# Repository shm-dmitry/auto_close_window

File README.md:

This project allows auto-open and auto-close your windows.
Project consists schematics of 3 modules and firmware for 2 controllers

Project re-started

In-door modules:
==============

1. Placed on window neare handle. It controls handle state (via hall sensor and magnet) and allows to you to push button open or close manually
Also this module connected to WIFI and allows to to control your window from any smart house server (via MQTT protocol).
2. Placed on up-side window frame. Contains servo, receives commands from module#1 and executes it.

Out-door module:
==============

1. Listen for a noise and check air quality. 

Project status
==============

| Hardware | status |
| ---- | ---- |
| Indoor schema :: near-handle module | no |
| Indoor schema :: servo module | no |
| Indoor schema :: digital channel to outdoor schema | no |
| Outdoor module schema :: microcontroller and its periphery | no |
| Outdoor module schema :: sensors | no |

| Board | status |
| ---- | ---- |
| Indoor board :: near-handle module | no |
| Indoor board :: servo module | no |
| Outdoor module board | no |

| Firmware | status |
| ---- | ---- |
| Indoor firmware :: hardware sensors - hall, switch and soft lock | no |
| Indoor firmware :: buttons | no |
| Indoor firmware :: servo control and calibration | no |
| Indoor firmware :: led indication | no |
| Indoor firmware :: controller | no |
| Outdoor firmware :: BMP280 | no |
| Outdoor firmware :: SGP30 | no |
| Outdoor firmware :: Noise sensor | no |
| Outdoor firmware :: Sensor value filters and controller | no |
| Outdoor firmware :: Data transmitter | no |

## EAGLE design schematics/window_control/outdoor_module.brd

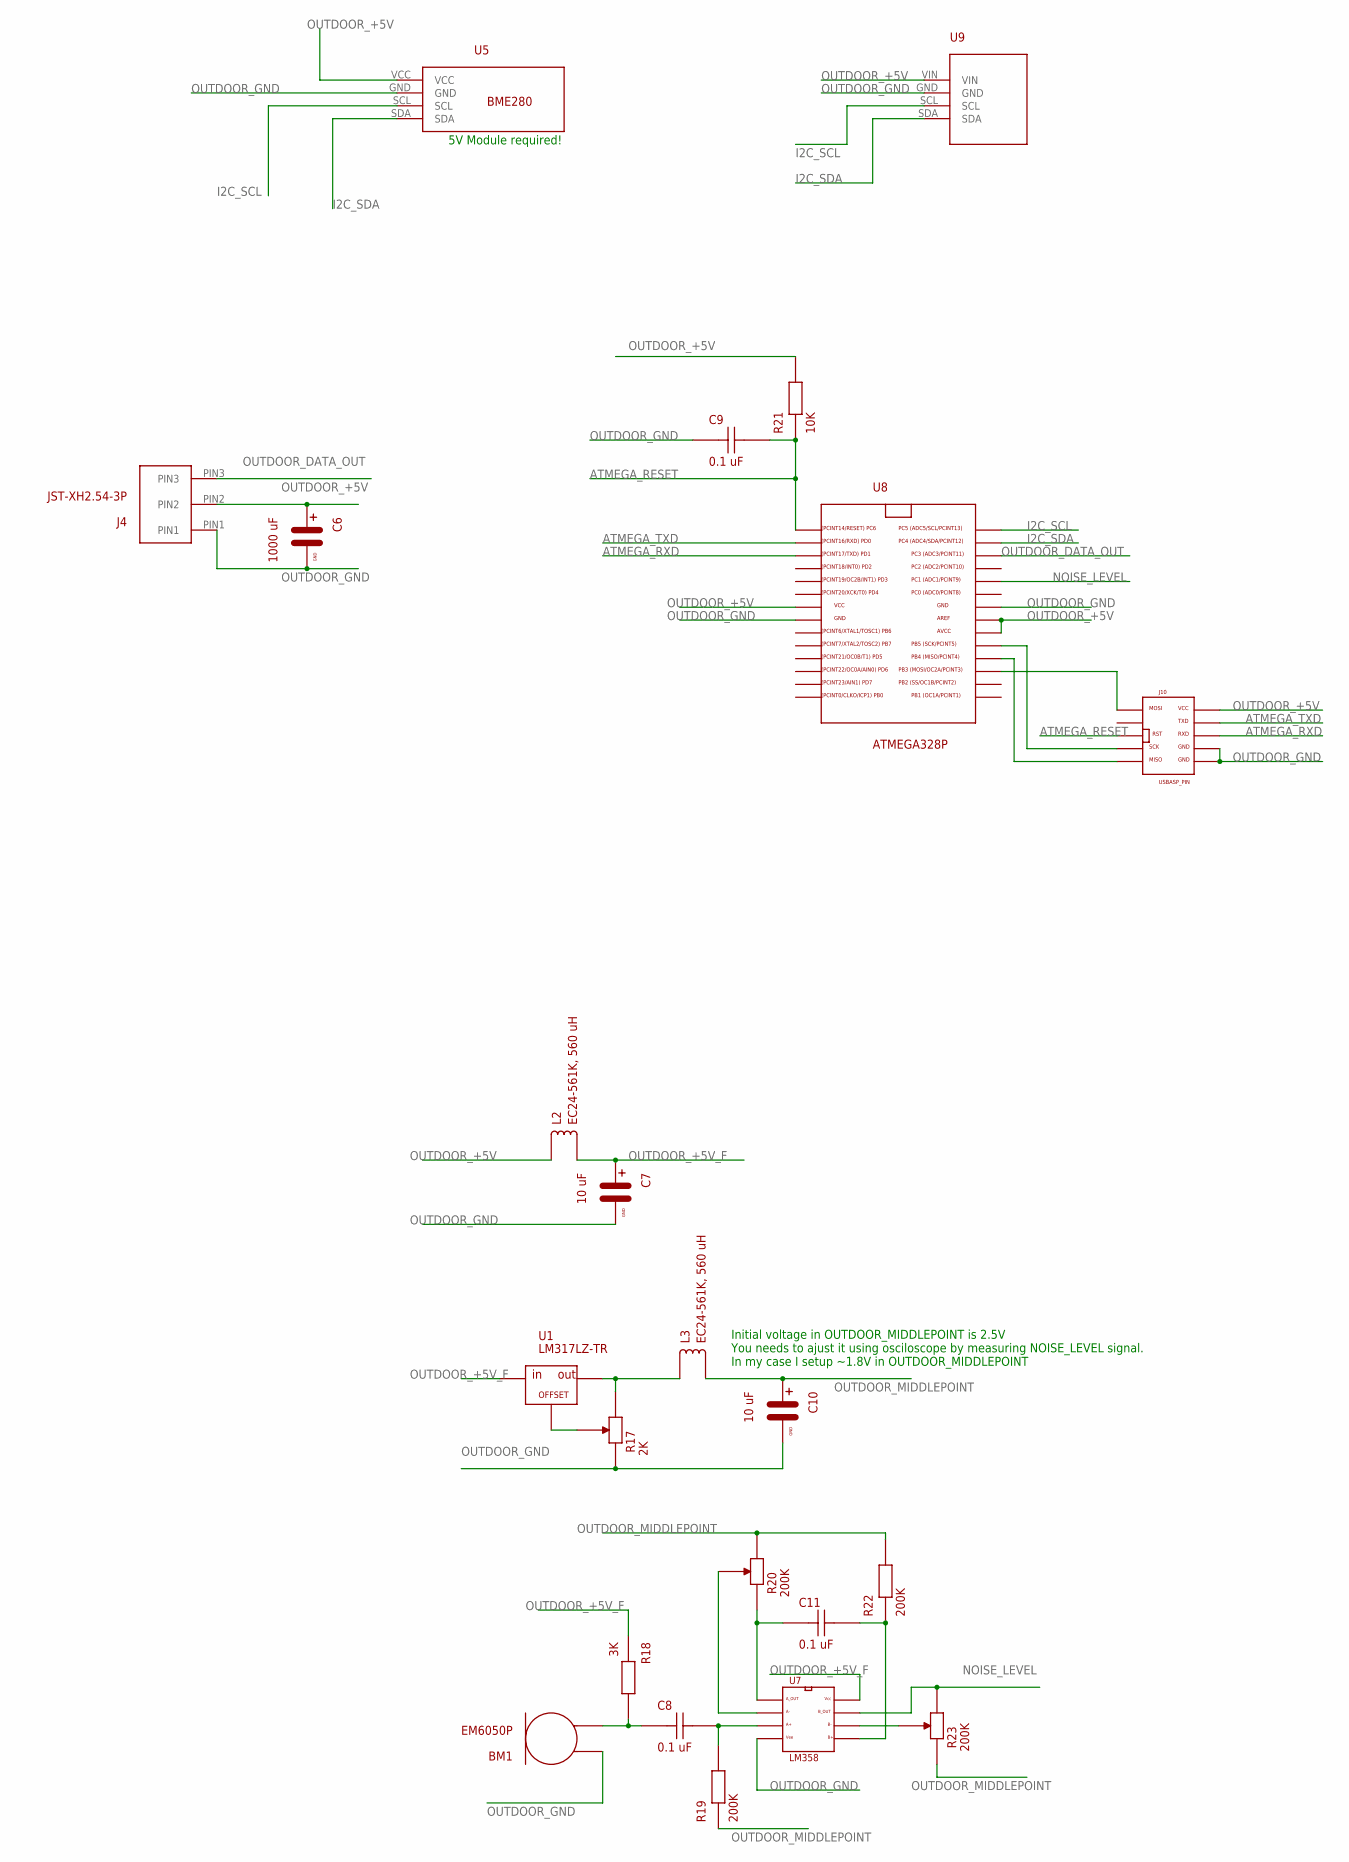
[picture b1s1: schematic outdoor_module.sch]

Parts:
BM1: EM6050P; MICROPHONE
C6: 1000 uF; C
C7, C10: 10 uF; C
C8, C9, C11: 0.1 uF; C-1
J4: JST-XH2.54-3P; JST-XH254-3P
J10: USBASP_PIN
L2, L3: EC24-561K, 560 uH; L-EC24
R17: 2K; RD-3362H
R18: 3K; R
R19, R22: 200K; R
R20, R23: 200K; RD-3296Z
R21: 10K; R
U1: LM317LZ-TR; TO-92
U5: BMP280 5V module; BME280-CONNECTOR-ONLY
U7: LM358; DIP8
U8: ATMEGA328P
U9: GY-SGP30

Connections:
ATMEGA_RESET: C9.P$2, J10.RST (RESET), R21.P$1, U8.PC6
ATMEGA_RXD: J10.RXD, U8.PD1
ATMEGA_TXD: J10.TXD, U8.PD0
I2C_SCL: U5.SCL, U8.PC5, U9.SCL
I2C_SDA: U5.SDA, U8.PC4, U9.SDA
unnamed: BM1.P$2, C8.P$1, R18.P$2
unnamed: C8.P$2, R19.P$2, U7.PIN_3 (A+)
unnamed: R17.P3, U1.P3 (GND)
unnamed: C11.P$1, R20.P1, U7.PIN_1 (A_OUT)
unnamed: R23.P3, U7.PIN_6 (B-)
unnamed: C11.P$2, R22.P$1, U7.PIN_5 (B+)
unnamed: R20.P3, U7.PIN_2 (A-)
unnamed: J10.MOSI, U8.PB3
unnamed: J10.MISO, U8.PB4
unnamed: J10.SCK, U8.PB5
NOISE_LEVEL: R23.P2, U7.PIN_7 (B_OUT), U8.PC1
OUT: L3.P$1, R17.P2, U1.P2 (OUT)
OUTDOOR_+5V: C6.PIN_PLUS, J4.PIN2, J10.VCC, L2.P$1, R21.P$2, U5.VCC, U8.AREF, U8.AVCC, U8.VCC, U9.VIN
OUTDOOR_+5V_F: C7.PIN_PLUS, L2.P$2, R18.P$1, U1.P1 (IN), U7.PIN_8 (VCC)
OUTDOOR_DATA_OUT: J4.PIN3, U8.PC3
OUTDOOR_GND: BM1.P$1, C6.PIN_GND, C7.PIN_GND, C9.P$1, C10.PIN_GND, J4.PIN1, J10.GND, J10.GND1, R17.P1, U5.GND, U7.PIN_4 (VEE), U8.GND, U8.GND1, U9.GND
OUTDOOR_MIDDLEPOINT: C10.PIN_PLUS, L3.P$2, R19.P$1, R20.P2, R22.P$2, R23.P1

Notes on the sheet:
5V Module required!
Initial voltage in OUTDOOR_MIDDLEPOINT is 2.5V You needs to ajust it using osciloscope by measuring NOISE_LEVEL signal. In my case I setup ~1.8V in OUTDOOR_MIDDLEPOINT

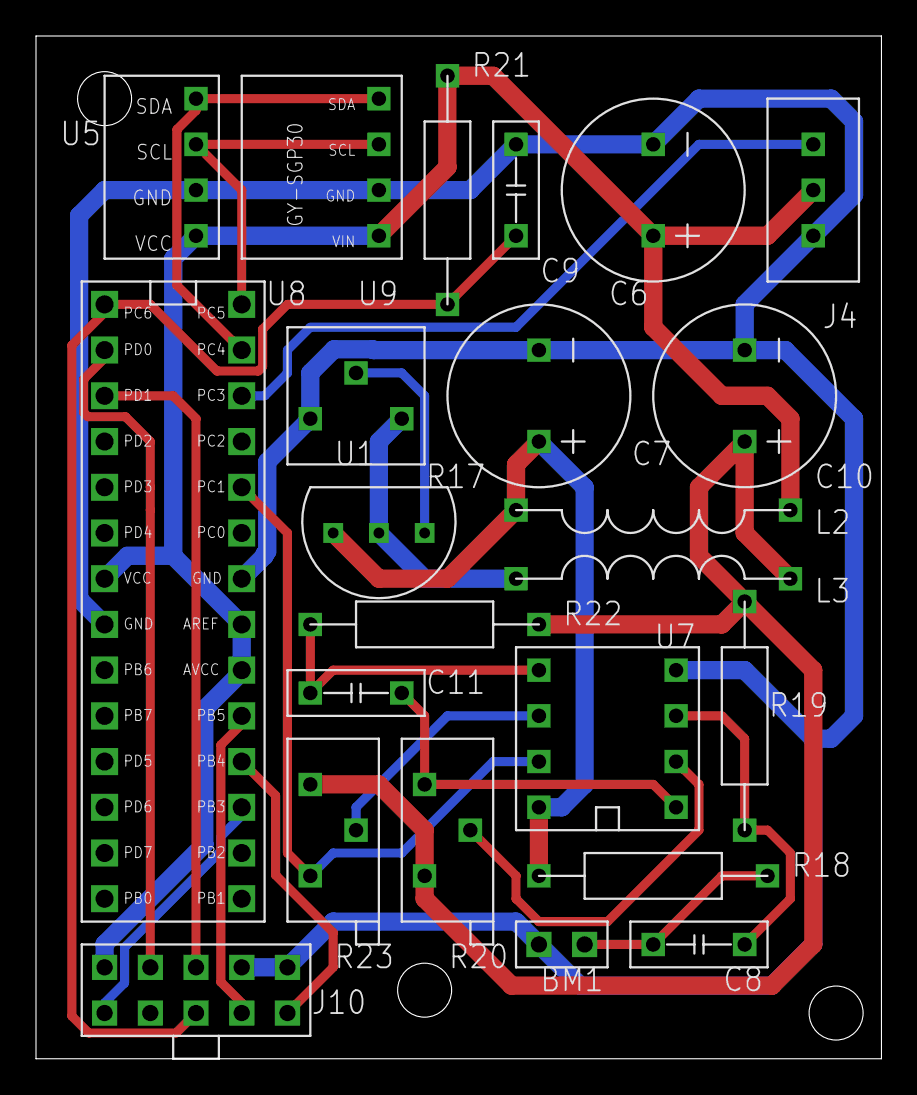
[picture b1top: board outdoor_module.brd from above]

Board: 2 copper layers, 47.0 x 56.8 mm, 23 parts (0 on the bottom side), 22 nets.

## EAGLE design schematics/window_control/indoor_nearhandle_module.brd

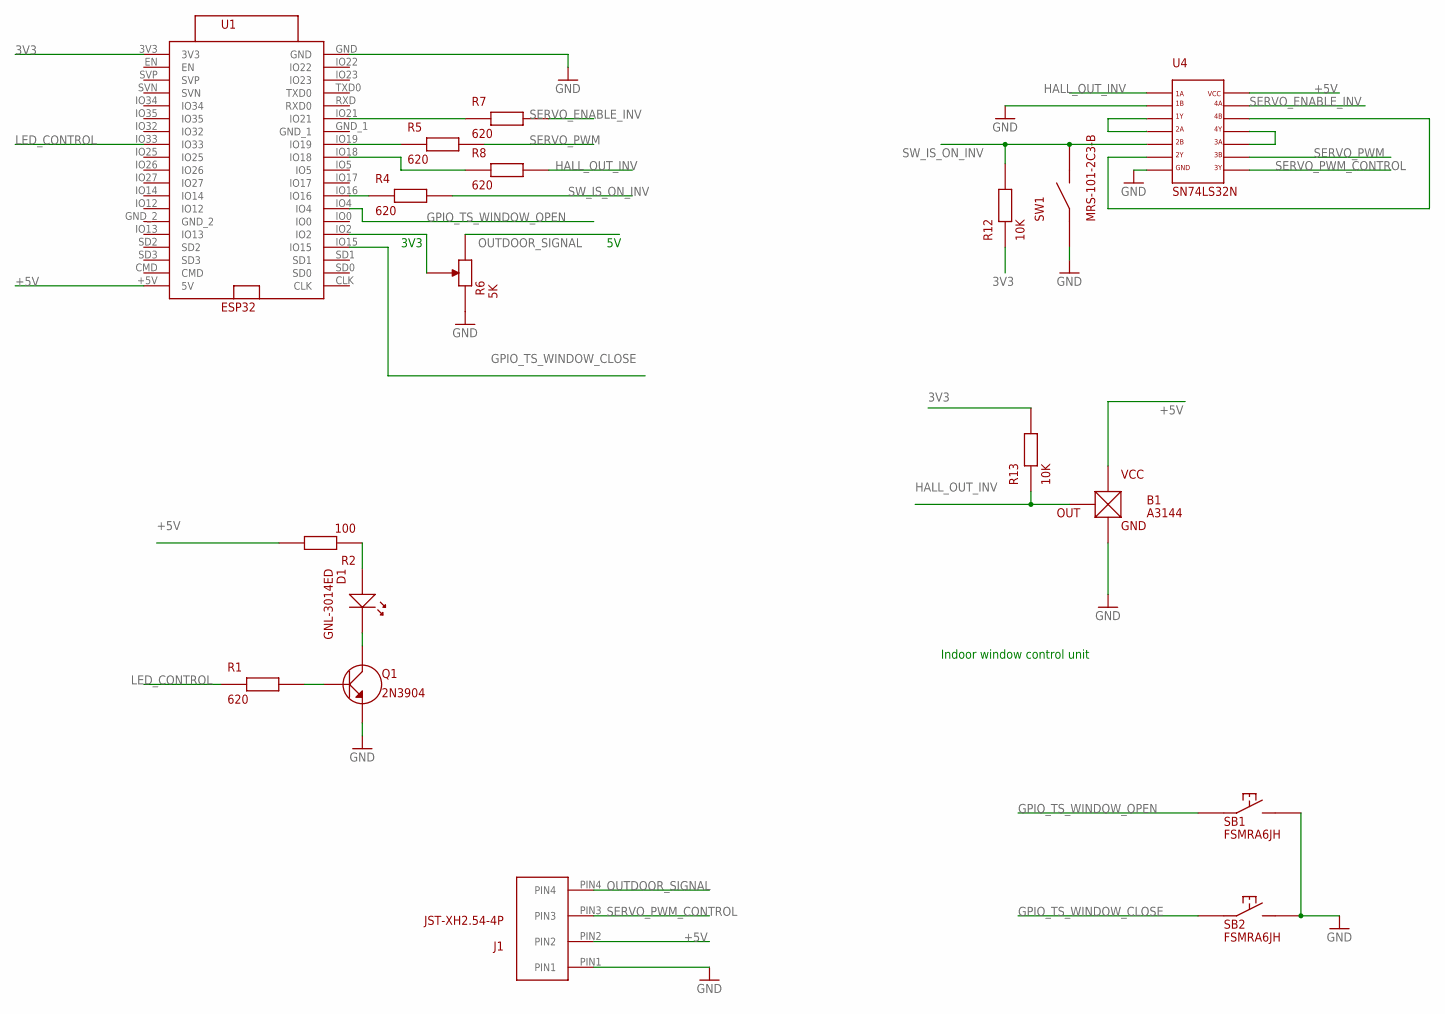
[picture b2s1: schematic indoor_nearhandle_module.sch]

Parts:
B1: A3144; HALL_SENSOR
D1: GNL-3014ED; LD
J1: JST-XH2.54-4P; JST-XH254-4P
Q1: 2N3904; TRANSISTOR
R1, R4, R5, R7, R8: 620; R
R2: 100; R
R6: 5K; RD-3362H
R12, R13: 10K; R
SB1, SB2: FSMRA6JH; SB-NO-SPST-ANGLE
SW1: MRS-101-2C3-B; SWITCH
U1: ESP32
U4: SN74LS32N; DIP14

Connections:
3V3: R12.P$1, R13.P$2, U1.3V3
+5V: B1.VCC, J1.PIN2, R2.P$2, U1.+5V (5V), U4.PIN_14 (VCC)
GND: B1.GND, J1.PIN1, Q1.E, R6.P1, SB1.B, SB2.B, SW1.P$1, U1.GND, U4.PIN_2 (1B), U4.PIN_7 (GND)
GPIO_TS_WINDOW_CLOSE: SB2.A, U1.IO15
GPIO_TS_WINDOW_OPEN: SB1.A, U1.IO4
HALL_OUT_INV: B1.OUT, R8.P$2, R13.P$1, U4.PIN_1 (1A)
LED_CONTROL: R1.P$1, U1.IO33
unnamed: U4.PIN_6 (2Y), U4.PIN_12 (4B)
unnamed: Q1.B, R1.P$2
unnamed: R5.P$1, U1.IO19
unnamed: D1.PIN_ANODE, Q1.C
unnamed: D1.PIN_CATHODE, R2.P$1
unnamed: R6.P3, U1.IO2
unnamed: R7.P$1, U1.IO21
unnamed: R8.P$1, U1.IO18
unnamed: R4.P$1, U1.IO16
unnamed: U4.PIN_10 (3A), U4.PIN_11 (4Y)
unnamed: U4.PIN_3 (1Y), U4.PIN_4 (2A)
OUTDOOR_SIGNAL: J1.PIN4, R6.P2
SERVO_ENABLE_INV: R7.P$2, U4.PIN_13 (4A)
SERVO_PWM: R5.P$2, U4.PIN_9 (3B)
SERVO_PWM_CONTROL: J1.PIN3, U4.PIN_8 (3Y)
SW_IS_ON_INV: R4.P$2, R12.P$2, SW1.P$2, U4.PIN_5 (2B)

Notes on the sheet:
Indoor window control unit
3V3

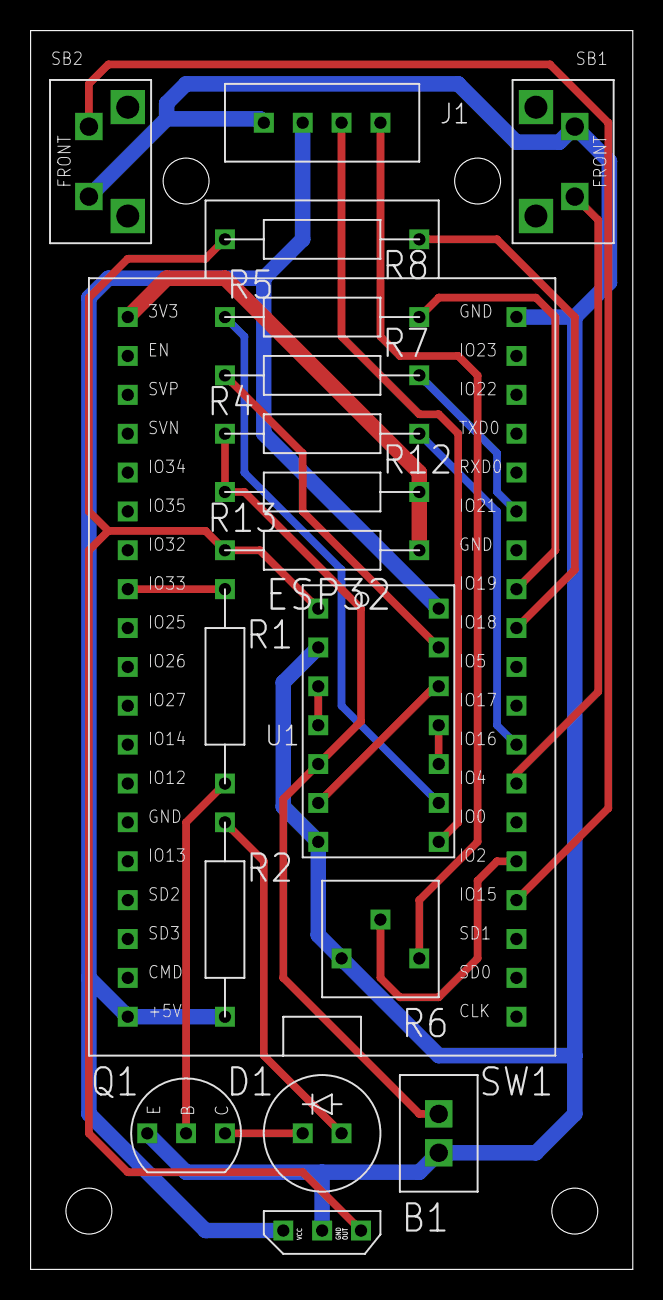
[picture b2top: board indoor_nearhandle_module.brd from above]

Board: 2 copper layers, 39.4 x 81.0 mm, 18 parts (0 on the bottom side), 23 nets.

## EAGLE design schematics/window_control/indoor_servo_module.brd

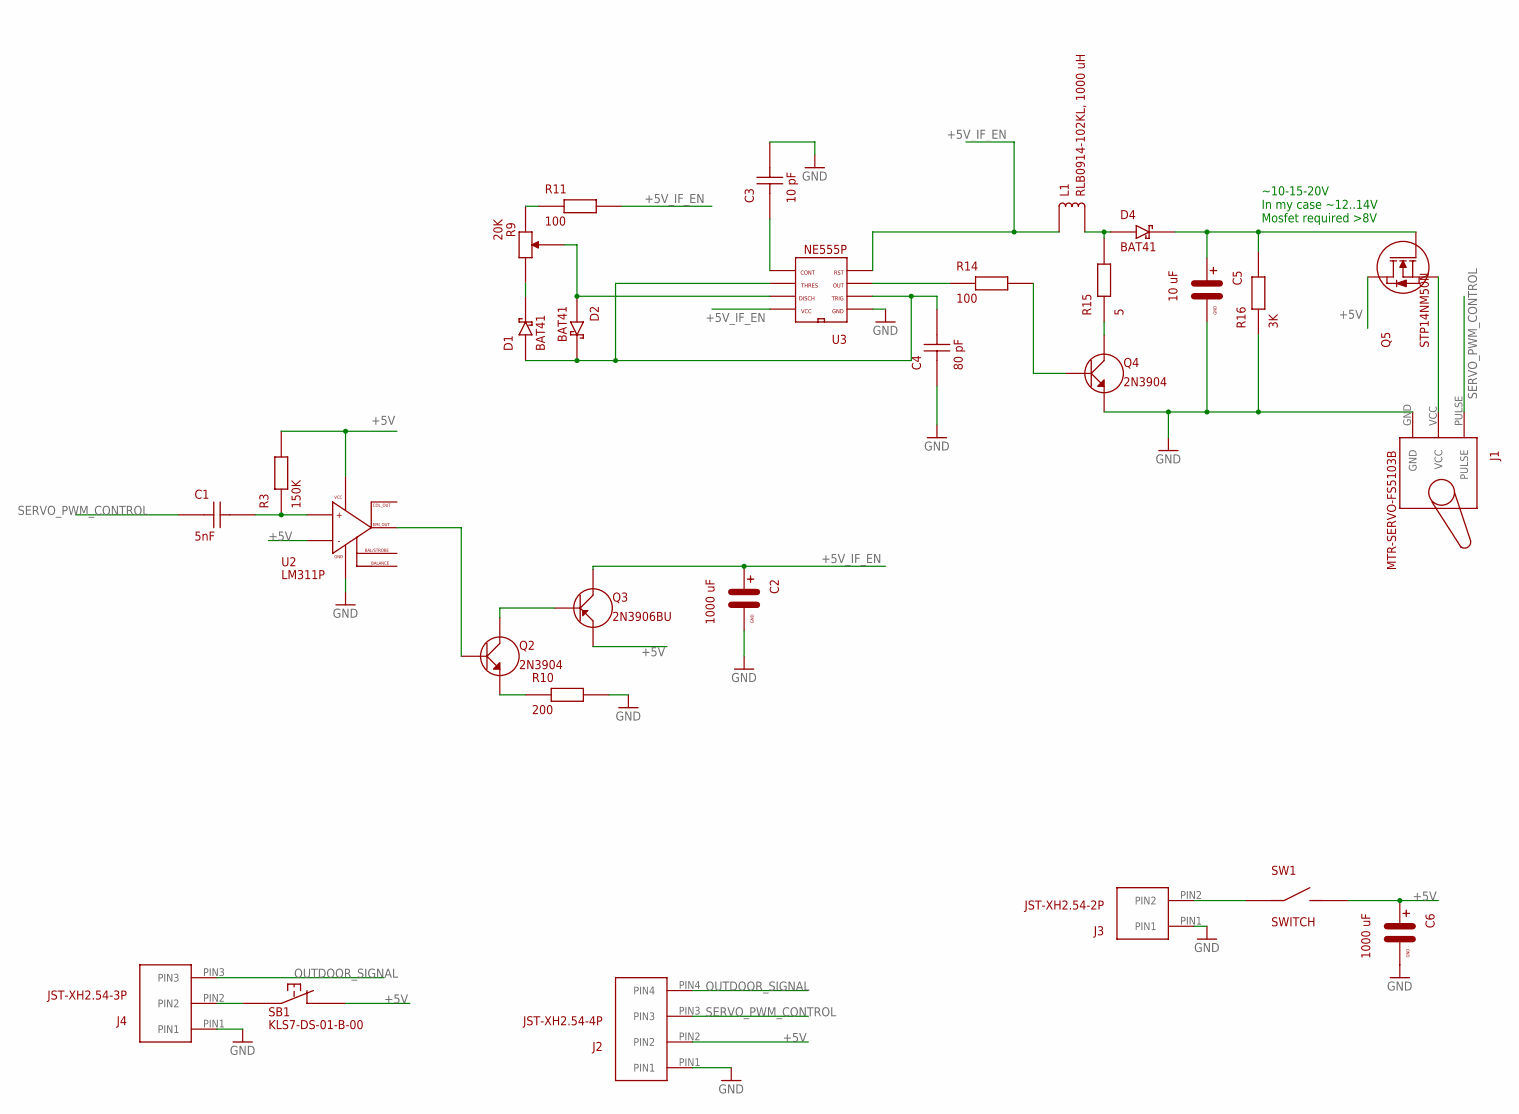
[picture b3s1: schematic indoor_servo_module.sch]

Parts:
C1: 5nF; C-1
C2, C6: 1000 uF; C
C3: 10 pF; C-1
C4: 80 pF; C-1
C5: 10 uF; C
D1, D2, D4: BAT41; D_SCHOTTKY
J1: MTR-SERVO-FS5103B; SERVO
J2: JST-XH2.54-4P; JST-XH254-4P
J3: JST-XH2.54-2P; JST-XH254-2P
J4: JST-XH2.54-3P; JST-XH254-3P
L1: RLB0914-102KL, 1000 uH; L-RLB0914
Q2, Q4: 2N3904; TRANSISTOR
Q3: 2N3906BU; TRANSISTOR
Q5: STP14NM50N; MOSFET_N
R3: 150K; R
R9: 20K; RD-3362H
R10: 200; R
R11, R14: 100; R
R15: 5; R
R16: 3K; R
SB1: KLS7-DS-01-B-00; SB-NC
SW1: SWITCH
U2: LM311P; DIP8
U3: NE555P; DIP8

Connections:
+5V: C6.PIN_PLUS, J2.PIN2, Q3.E, Q5.D, R3.P$2, SB1.P$2, SW1.P$2, U2.PIN_3 (IN-), U2.PIN_8 (VCC)
+5V_IF_EN: C2.PIN_PLUS, L1.P$1, Q3.C, R11.P$2, U3.PIN_4 (RESET), U3.PIN_8 (VCC)
GND: C2.PIN_GND, C3.P$2, C4.P$1, C5.PIN_GND, C6.PIN_GND, J1.GND, J2.PIN1, J3.PIN1, J4.PIN1, Q4.E, R10.P$2, R16.P$1, U2.PIN_4 (GND), U3.PIN_1 (GND)
unnamed: Q4.C, R15.P$1
unnamed: Q4.B, R14.P$2
unnamed: J3.PIN2, SW1.P$1
unnamed: J4.PIN2, SB1.P$1
unnamed: R14.P$1, U3.PIN_3 (OUT)
unnamed: Q2.C, Q3.B
unnamed: Q2.E, R10.P$1
unnamed: D4.ANODE, L1.P$2, R15.P$2
unnamed: J1.VCC, Q5.S
unnamed: C3.P$1, U3.PIN_5 (CONT)
unnamed: C4.P$2, D1.ANODE, D2.CATHODE, U3.PIN_2 (TRIG), U3.PIN_6 (THRES)
unnamed: D2.ANODE, R9.P3, U3.PIN_7 (DISCH)
unnamed: D1.CATHODE, R9.P2
unnamed: R9.P1, R11.P$1
unnamed: Q2.B, U2.PIN_1 (EMI_OUT)
unnamed: C5.PIN_PLUS, D4.CATHODE, Q5.G, R16.P$2
unnamed: C1.P$2, R3.P$1, U2.PIN_2 (IN+)
OUTDOOR_SIGNAL: J2.PIN4, J4.PIN3
SERVO_PWM_CONTROL: C1.P$1, J1.PULSE, J2.PIN3

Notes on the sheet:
~10-15-20V In my case ~12..14V Mosfet required >8V

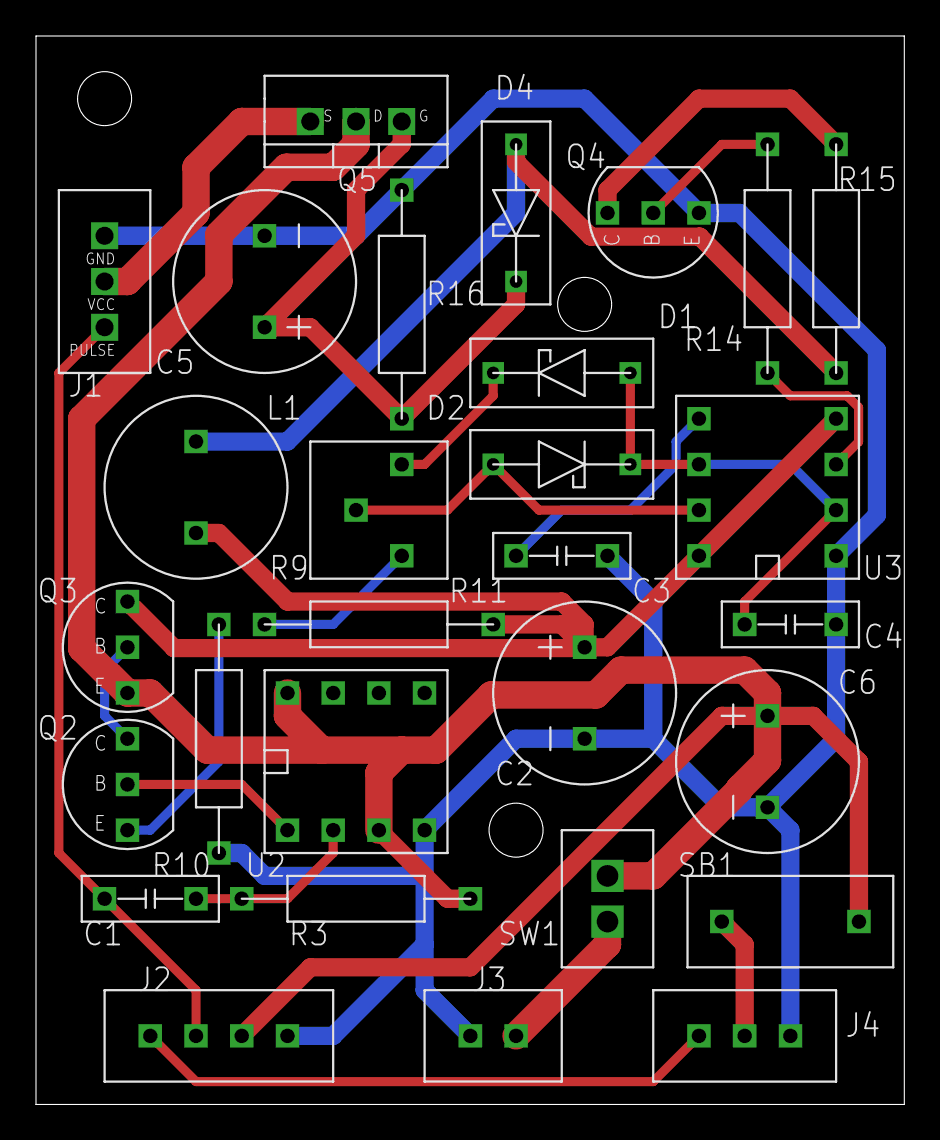
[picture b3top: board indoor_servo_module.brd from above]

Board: 2 copper layers, 48.2 x 59.4 mm, 29 parts (0 on the bottom side), 22 nets.

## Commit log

2021-07-27 Continue working under schematics
2021-07-27 Added driver for servo FS5103B
2021-07-29 working under schematics
2021-08-03 1. working under schematics. 2. ESP32 firmware writen but not tested yet. 3. I conntected to ATMega controller and uploaded test firmware to it
2021-08-03 stop servo on full-open and full-close positions
2021-08-04 Start debugging process
2021-08-04 Indoor modules schematics and firmware works now!
2021-08-05 Preparing to debug ATMega controller. I have no JTAG, and USBasp does not allows debugging. I will try to use 443 MHZ transmitter and 433 Mhz receiver on raspberry pi as debug terminal :)
2021-08-08 Start writing firmware for outdoor module
2021-08-13 SGP30 Module works now
2021-08-13 I checked several pins_arduino.h, but only this works fine. Thanks to https://github.com/MCUdude/MightyCore
2021-08-13 Remove unused file
2021-08-17 actualized schematics of outdoor noise sensor module
2021-08-17 actualized some nominals in schematics
2021-08-22 BMP280 works now
2021-09-26 Changed Noise sensor schematics. Removed MSGEQ7 chip (replaced with program FFT). I cant find any live. Changed Volume Amplifier from transistors to chio.
2021-09-26 Noise sensor works
2021-09-27 added initially code for filter and encrypter components
2021-10-30 changed schematics. Removed 433MHZ transmitter. Outdoor module will transfer data using ESP32
2021-10-30 Added code to send data from AVR to ESP32
2021-10-30 Estabilished connection between AVR and ESP32. ESP32 ready to read data from AVR and send it into MQTT
2021-10-31 Change noise sensor schema
2021-11-04 changed microcontroller to ATMEGA328P to reduce device size
2021-11-04 Added TX and RX links from USBASP to ATMEGA
2021-11-04 Firmware and ATMega connection are synchronized. USBasp works successfully
2021-11-04 full schema on atmega328 tested and worked
2021-11-05 Start boards preparing - actualized new element dimentions
2021-11-05 Touch sensor are unstable. I made a decision to replace it by normally-open buttons
2021-11-06 Added button borders and nominals
2021-11-07 Start working under first border
2021-11-07 Board redesigned to reduce it width
2021-11-07 Indoor board - ready
2021-11-07 Indoor board - added ground polygon
2021-11-07 Start working under second border
2021-11-08 Servo module ready, but i will change connectors
2021-11-08 Servo module - added holes
2021-11-08 Added board for outdoor module
2021-11-08 Connectors changed
2021-11-08 Fixed issue in one border - all supply lines now connected to capacity only. And from filter capacity power goes to another elements.
2021-11-08 Increased supply line size to servo
2021-11-08 Outdoor module board size reduced
2021-11-08 Changes in library
2021-11-09 Start preparing to order boards. Checked all labels
2021-11-09 Boards checked and ready to order
2021-11-09 Holes moved away from board border
2021-12-17 Touchpad driver replaced by buttons driver.
2021-12-17 Removed unused constants. Updated eagle library
2021-12-17 hear handle module & indoor servo module assembled and checked
2021-12-17 fixed error in outdoor board and schema
2021-12-17 actualized voltage regulator nominal
2021-12-18 Added 3D models
2021-12-19 3D models for box
2021-12-21 Updated 3D models
2021-12-23 Continue working under 3D models
2021-12-24 3D models
2021-12-25 Fixed errors in 3D model connector betwween servo handler and window
2021-12-29 changes in 3D models
2021-12-29 removed test models
2021-12-30 fixed error in servo box
2021-12-31 Ok, I think I finished with indoor 3D models. Outdoor box printing reuqired.
2023-08-22 Project re-startefd
2023-08-23 start create schematics
2023-09-11 Creating schematics and boards
2023-09-12 Second board
2023-09-12 changes in second board
2023-11-02 Project prepared to order
2023-11-29 first version of main-module firmware. not tested yet.
2023-11-29 Encryption code moved from my another project
2023-11-29 I readed 1527 code... in bit-form, but it works.
2023-11-30 FM debugging - intermediate result
2023-12-01 Transmitter/receiver are stable
2023-12-01 assigned different addresses
2023-12-01 added 2 addresses for charger process
2023-12-01 charger tested
2023-12-01 WIFI & NQTT integration
2023-12-01 MQTT integration
2023-12-05 1. start working under handle module; 2. rewrite stepper driver
2023-12-05 Led integration in handle-module
2023-12-06 stepper driver re-writed
2023-12-06 range-checks and define constants in stepper
2023-12-08 Working under firmwares
2023-12-08 HM and MM starts to try work together
2023-12-11 1. first 3D models, 2. charger works
2023-12-11 change nominal
2023-12-13 Working under 3d models
2023-12-14 1. Fixed schema - limit switch connection moved to ADC pin
2023-12-18 Working under firmware
2023-12-25 Prepare to fix error with window position
2023-12-25 several models updated
2023-12-26 firmware works (at least I think so)
2024-01-07 Adjust models to my window
2024-03-07 models
2024-04-05 prepare to rewrite charing schema
2024-04-09 1. board: added protection against high noise in case of endstop is broken. 2. board: added step-up 7.5V -> 15V for charger. 3. firmware - added support for noise protection and some changes in stepp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
2024-04-09 few comments in source code
2024-04-09 added deglich in noise protection.
2024-04-10 Firmware uploaded and tested on the board (without noise sensor at this moment)
2024-04-11 1. added OTA; 2. debug log messages removed from release build using additional flag
2024-05-11 another iteration for outdorr and handle modules
2024-05-14 removed blind vias - it's production is too expensive
2024-07-24 charger (logic path) works normally
2024-07-24 added 'limit switch connected' logic
2024-07-25 noise alarm changes after hardware test
2024-07-25 remove lock file from repository
2024-07-26 firmware adapted to new hardware
2024-07-26 start debugging fm@315 on mm-side
2024-08-28 handle module & main module almost done
2024-08-29 prepare to change ADC working mode to continuus
2024-09-02 ADC logic changed from opeshot to async continuos. This change stabilazed limit switch logic.
2024-09-12 i found problems with 315MHZ freq (some transmitter blocks air near me). So I added another remote control and I will create box for it
2024-09-16 Fixes in models
2024-09-23 adding auto-hide mechanics allows to remove lock mechanizm from window way in unlocked state
2024-10-02 changes in firmware; changes in 3D models
2024-10-02 updated status message topics, updated my configuration example
2024-10-03 added ability to stop processing PDU messages in case of someone wants to spam the air
2024-10-03 drill template fixed
2024-10-09 3D models re-exported
2024-10-14 1. publish initial state after startup; 2. changes in 3D model after testing
2024-11-01 change mm-box to use power cabel
2024-11-01 fix PDU buttons mapping
2024-11-05 before plate update
2024-11-05 change holes in plate
2024-11-12 processing pre-release check, models updated
2024-11-22 added ability to enable/disable steppers on endstop positions
